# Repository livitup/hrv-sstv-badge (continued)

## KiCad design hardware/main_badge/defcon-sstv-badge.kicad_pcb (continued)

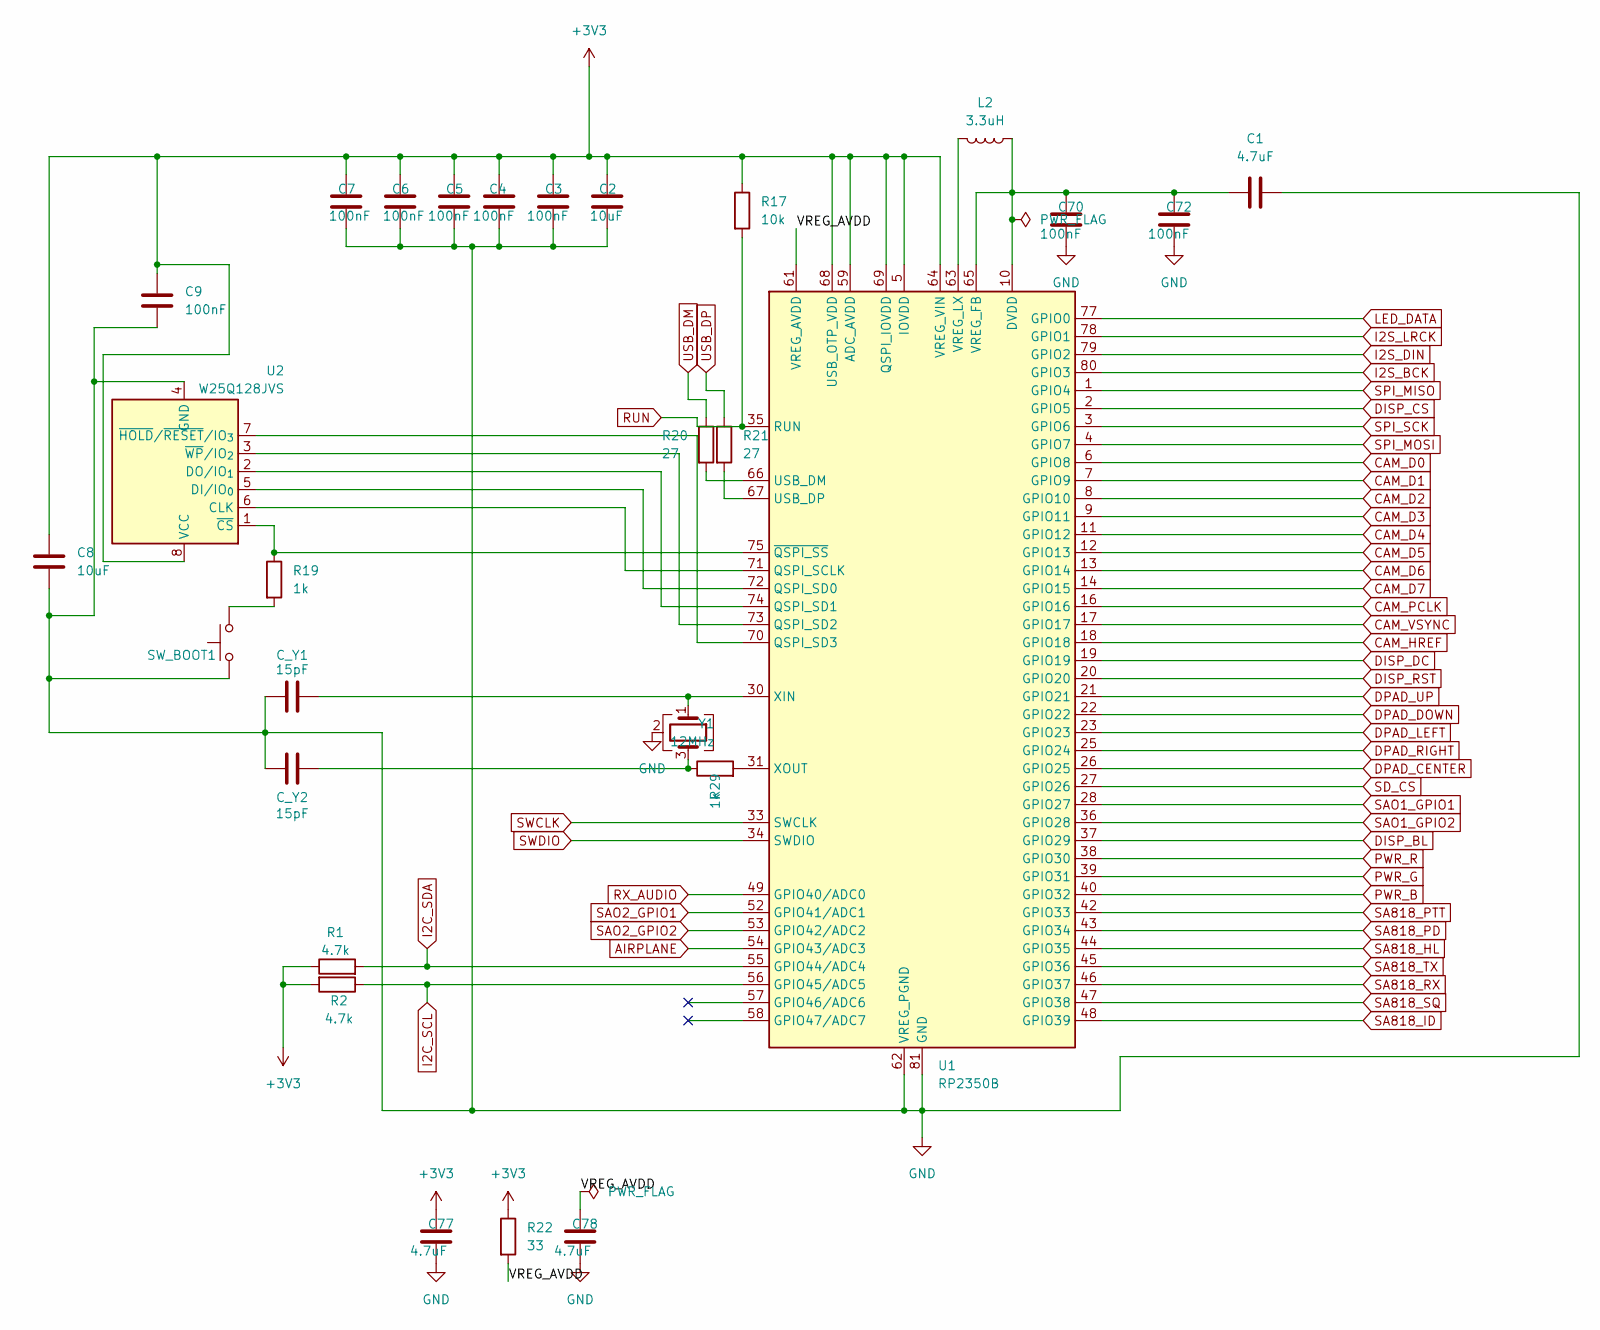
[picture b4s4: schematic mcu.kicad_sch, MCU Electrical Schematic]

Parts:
C1, C77: 4.7uF; C_0402_1005Metric_Wide
C2: 10uF; C_0603_1608Metric
C3, C4, C5, C6, C7, C9, C70, C72: 100nF; C_0402_1005Metric
C8: 10uF; C_0805_2012Metric
C78: 4.7uF; C_0402_1005Metric
C_Y1, C_Y2: 15pF; C_0402_1005Metric
L2: 3.3uH; L_Abracon_AOTA-B201610
R1, R2: 4.7k; R_0603_1608Metric
R17: 10k; R_0603_1608Metric
R19, R29: 1k; R_0402_1005Metric
R20, R21: 27; R_0402_1005Metric
R22: 33; R_0402_1005Metric
SW_BOOT1: SW_Push; SW_SPST_CK_RS282G05A3
U1: RP2350B; QFN-80-1EP_10x10mm_P0.4mm_EP3.4x3.4mm
U2: W25Q128JVS; SOIC-8_5.3x5.3mm_P1.27mm
Y1: 12MHz; Crystal_SMD_3225-4Pin_3.2x2.5mm

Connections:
+3V3: C2.1, C3.1, C4.1, C5.1, C6.1, C7.1, C8.1, C9.1, C77.1, R1.1, R2.2, R17.1, R22.1, U1.5 (IOVDD), U1.15 (IOVDD), U1.24 (IOVDD), U1.29 (IOVDD), U1.41 (IOVDD), U1.50 (IOVDD), U1.59 (ADC_AVDD), U1.60 (IOVDD), U1.64 (VREG_VIN), U1.68 (USB_OTP_VDD), U1.69 (QSPI_IOVDD), U1.76 (IOVDD), U2.8 (VCC); also elsewhere on the board
/MCU/VREG_AVDD: C78.1, R22.2, U1.61 (VREG_AVDD)
AIRPLANE: U1.54 (GPIO43/ADC3); also elsewhere on the board
CAM_D0: U1.6 (GPIO8); also elsewhere on the board
CAM_D1: U1.7 (GPIO9); also elsewhere on the board
CAM_D2: U1.8 (GPIO10); also elsewhere on the board
CAM_D3: U1.9 (GPIO11); also elsewhere on the board
CAM_D4: U1.11 (GPIO12); also elsewhere on the board
CAM_D5: U1.12 (GPIO13); also elsewhere on the board
CAM_D6: U1.13 (GPIO14); also elsewhere on the board
CAM_D7: U1.14 (GPIO15); also elsewhere on the board
CAM_HREF: U1.18 (GPIO18); also elsewhere on the board
CAM_PCLK: U1.16 (GPIO16); also elsewhere on the board
CAM_VSYNC: U1.17 (GPIO17); also elsewhere on the board
DISP_BL: U1.37 (GPIO29); also elsewhere on the board
DISP_CS: U1.2 (GPIO5); also elsewhere on the board
DISP_DC: U1.19 (GPIO19); also elsewhere on the board
DISP_RST: U1.20 (GPIO20); also elsewhere on the board
DPAD_CENTER: U1.26 (GPIO25); also elsewhere on the board
DPAD_DOWN: U1.22 (GPIO22); also elsewhere on the board
DPAD_LEFT: U1.23 (GPIO23); also elsewhere on the board
DPAD_RIGHT: U1.25 (GPIO24); also elsewhere on the board
DPAD_UP: U1.21 (GPIO21); also elsewhere on the board
I2C_SCL: R2.1, U1.56 (GPIO45/ADC5); also elsewhere on the board
I2C_SDA: R1.2, U1.55 (GPIO44/ADC4); also elsewhere on the board
I2S_BCK: U1.80 (GPIO3); also elsewhere on the board
I2S_DIN: U1.79 (GPIO2); also elsewhere on the board
I2S_LRCK: U1.78 (GPIO1); also elsewhere on the board
LED_DATA: U1.77 (GPIO0); also elsewhere on the board
unnamed: C_Y2.2, R29.1, Y1.3
unnamed: R19.2, SW_BOOT1.2
unnamed: U1.71 (QSPI_SCLK), U2.6 (CLK)
unnamed: U1.72 (QSPI_SD0), U2.5 (DI/IO_{0})
unnamed: U1.74 (QSPI_SD1), U2.2 (DO/IO_{1})
unnamed: U1.73 (QSPI_SD2), U2.3 (~WP/IO_{2})
unnamed: U1.70 (QSPI_SD3), U2.7 (~HOLD/~RESET/IO_{3})
unnamed: R20.2, U1.66 (USB_DM)
unnamed: R21.2, U1.67 (USB_DP)
unnamed: C1.1, C70.1, C72.1, L2.1, U1.10 (DVDD), U1.32 (DVDD), U1.51 (DVDD), U1.65 (VREG_FB)
unnamed: L2.2, U1.63 (VREG_LX)
unnamed: C_Y1.2, U1.30 (XIN), Y1.1
unnamed: R29.2, U1.31 (XOUT)
unnamed: R19.1, U1.75 (~QSPI_SS), U2.1 (~CS)
PWR_B: U1.40 (GPIO32); also elsewhere on the board
PWR_G: U1.39 (GPIO31); also elsewhere on the board
PWR_R: U1.38 (GPIO30); also elsewhere on the board
RUN: R17.2, U1.35 (RUN); also elsewhere on the board
RX_AUDIO: U1.49 (GPIO40/ADC0); also elsewhere on the board
SA818_HL: U1.44 (GPIO35); also elsewhere on the board
SA818_ID: U1.48 (GPIO39); also elsewhere on the board
SA818_PD: U1.43 (GPIO34); also elsewhere on the board
SA818_PTT: U1.42 (GPIO33); also elsewhere on the board
SA818_RX: U1.46 (GPIO37); also elsewhere on the board
SA818_SQ: U1.47 (GPIO38); also elsewhere on the board
SA818_TX: U1.45 (GPIO36); also elsewhere on the board
SAO1_GPIO1: U1.28 (GPIO27); also elsewhere on the board
SAO1_GPIO2: U1.36 (GPIO28); also elsewhere on the board
SAO2_GPIO1: U1.52 (GPIO41/ADC1); also elsewhere on the board
SAO2_GPIO2: U1.53 (GPIO42/ADC2); also elsewhere on the board
SD_CS: U1.27 (GPIO26); also elsewhere on the board
SPI_MISO: U1.1 (GPIO4); also elsewhere on the board
SPI_MOSI: U1.4 (GPIO7); also elsewhere on the board
SPI_SCK: U1.3 (GPIO6); also elsewhere on the board
SWCLK: U1.33 (SWCLK); also elsewhere on the board
SWDIO: U1.34 (SWDIO); also elsewhere on the board
USB_DM: R20.1; also elsewhere on the board
USB_DP: R21.1; also elsewhere on the board

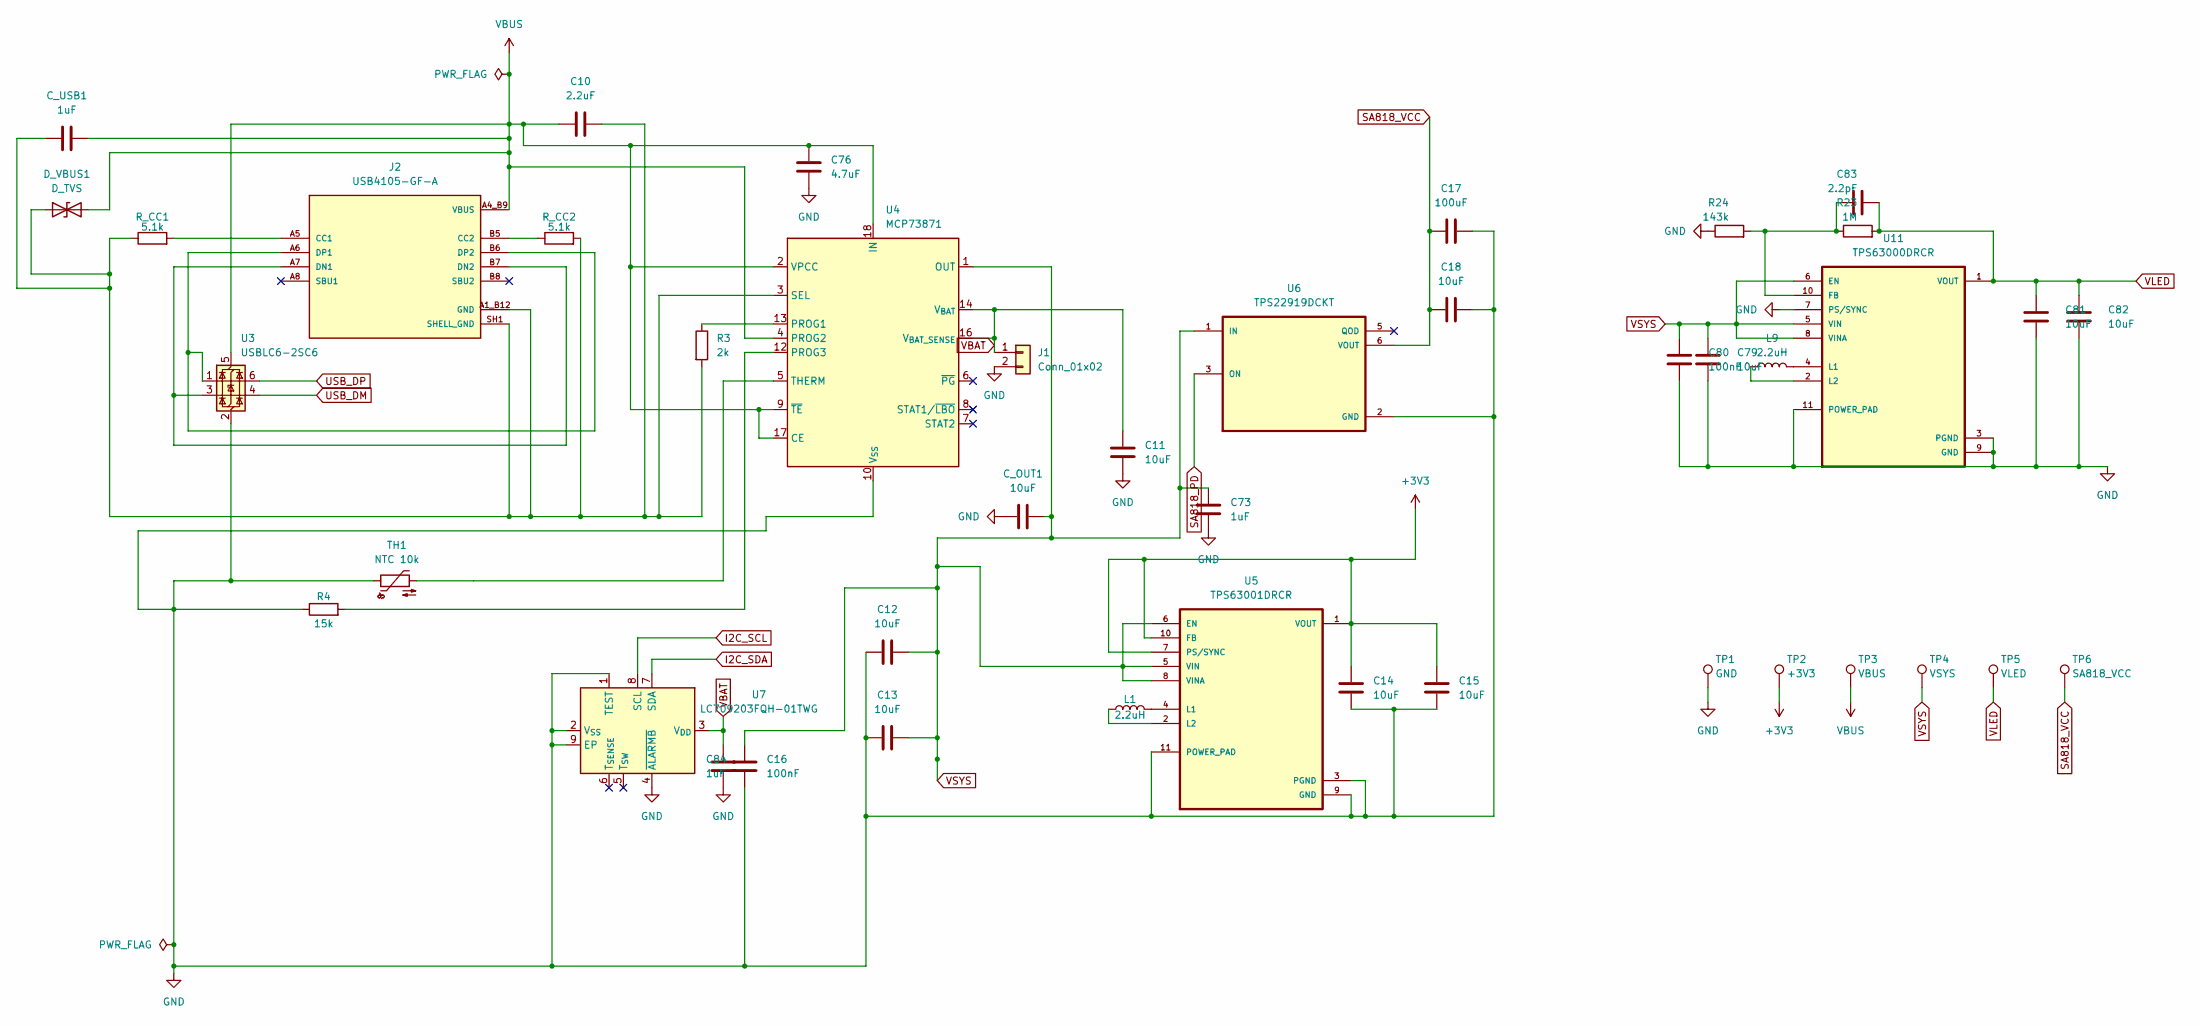
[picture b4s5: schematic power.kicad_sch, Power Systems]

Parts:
C10: 2.2uF; C_0805_2012Metric
C11, C12, C13, C14, C15, C79, C81, C82: 10uF; C_0805_2012Metric
C16, C80: 100nF; C_0402_1005Metric
C17: 100uF; C_1206_3216Metric
C18: 10uF; C_0603_1608Metric
C73: 1uF; C_0603_1608Metric
C76: 4.7uF; C_0603_1608Metric
C83: 2.2pF; C_0402_1005Metric
C84: 1uF; C_0402_1005Metric
C_OUT1: 10uF; C_0805_2012Metric
C_USB1: 1uF; C_0603_1608Metric
D_VBUS1: D_TVS; D_SOD-323
J1: Conn_01x02; JST_PH_S2B-PH-SM4-TB_1x02-1MP_P2.00mm_Horizontal
J2: USB4105-GF-A; GCT_USB4105-GF-A; PARTREV B4
L1, L9: 2.2uH; L_Taiyo-Yuden_NR-30xx_HandSoldering
R3: 2k; R_0603_1608Metric
R4: 15k; R_0603_1608Metric
R23: 1M; R_0603_1608Metric
R24: 143k; R_0603_1608Metric
R_CC1, R_CC2: 5.1k; R_0402_1005Metric
TH1: NTC 10k; R_0603_1608Metric
TP1: GND; TestPoint_Pad_D1.0mm
TP2: +3V3; TestPoint_Pad_D1.0mm
TP3: VBUS; TestPoint_Pad_D1.0mm
TP4: VSYS; TestPoint_Pad_D1.0mm
TP5: VLED; TestPoint_Pad_D1.0mm
TP6: SA818_VCC; TestPoint_Pad_D1.0mm
U3: USBLC6-2SC6; SOT-23-6
U4: MCP73871; QFN-20-1EP_4x4mm_P0.5mm_EP2.5x2.5mm
U5: TPS63001DRCR; VREG_V62_16624-01YE
U6: TPS22919DCKT; SOT65P210X110-6N
U7: LC709203FQH-01TWG; WDFN-8-1EP_4x3mm_P0.65mm_EP2.4x1.8mm
U11: TPS63000DRCR; VREG_V62_16624-01YE

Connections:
+3V3: C14.1, C15.1, TP2.1, U5.1 (VOUT), U5.7 (PS/SYNC), U5.10 (FB); also elsewhere on the board
I2C_SCL: U7.8 (SCL); also elsewhere on the board
I2C_SDA: U7.7 (SDA); also elsewhere on the board
unnamed: J2.A5 (CC1), R_CC1.2
unnamed: J2.B5 (CC2), R_CC2.1
unnamed: J2.A7 (DN1), J2.B7 (DN2), U3.3 (I/O2)
unnamed: J2.A6 (DP1), J2.B6 (DP2), U3.1 (I/O1)
unnamed: R3.1, U4.13 (PROG1)
unnamed: R4.2, U4.12 (PROG3)
unnamed: TH1.2, U4.5 (THERM)
unnamed: L1.2, U5.4 (L1)
unnamed: L1.1, U5.2 (L2)
unnamed: C83.1, R23.1, R24.2, U11.10 (FB)
unnamed: L9.2, U11.4 (L1)
unnamed: L9.1, U11.2 (L2)
SA818_PD: U6.3 (ON); also elsewhere on the board
SA818_VCC: C17.1, C18.1, TP6.1, U6.6 (VOUT); also elsewhere on the board
USB_DM: U3.4 (I/O2); also elsewhere on the board
USB_DP: U3.6 (I/O1); also elsewhere on the board
VBAT: C11.1, C84.1, J1.1, U4.14 (V_{BAT}), U4.15 (V_{BAT}), U4.16 (V_{BAT_SENSE}), U7.3 (V_{DD})
VBUS: C10.1, C76.1, C_USB1.2, D_VBUS1.2 (A2), J2.A4_B9 (VBUS), J2.B4_A9 (VBUS), TP3.1, U3.5 (VBUS), U4.2 (VPCC), U4.4 (PROG2), U4.9 (~TE), U4.17 (CE), U4.18 (IN), U4.19 (IN)
VLED: C81.1, C82.1, C83.2, R23.2, TP5.1, U11.1 (VOUT); also elsewhere on the board
VSYS: C12.1, C13.2, C16.1, C73.1, C79.1, C80.1, C_OUT1.1, TP4.1, U4.1 (OUT), U4.20 (OUT), U5.5 (VIN), U5.6 (EN), U5.8 (VINA), U6.1 (IN), U11.5 (VIN), U11.6 (EN), U11.8 (VINA)

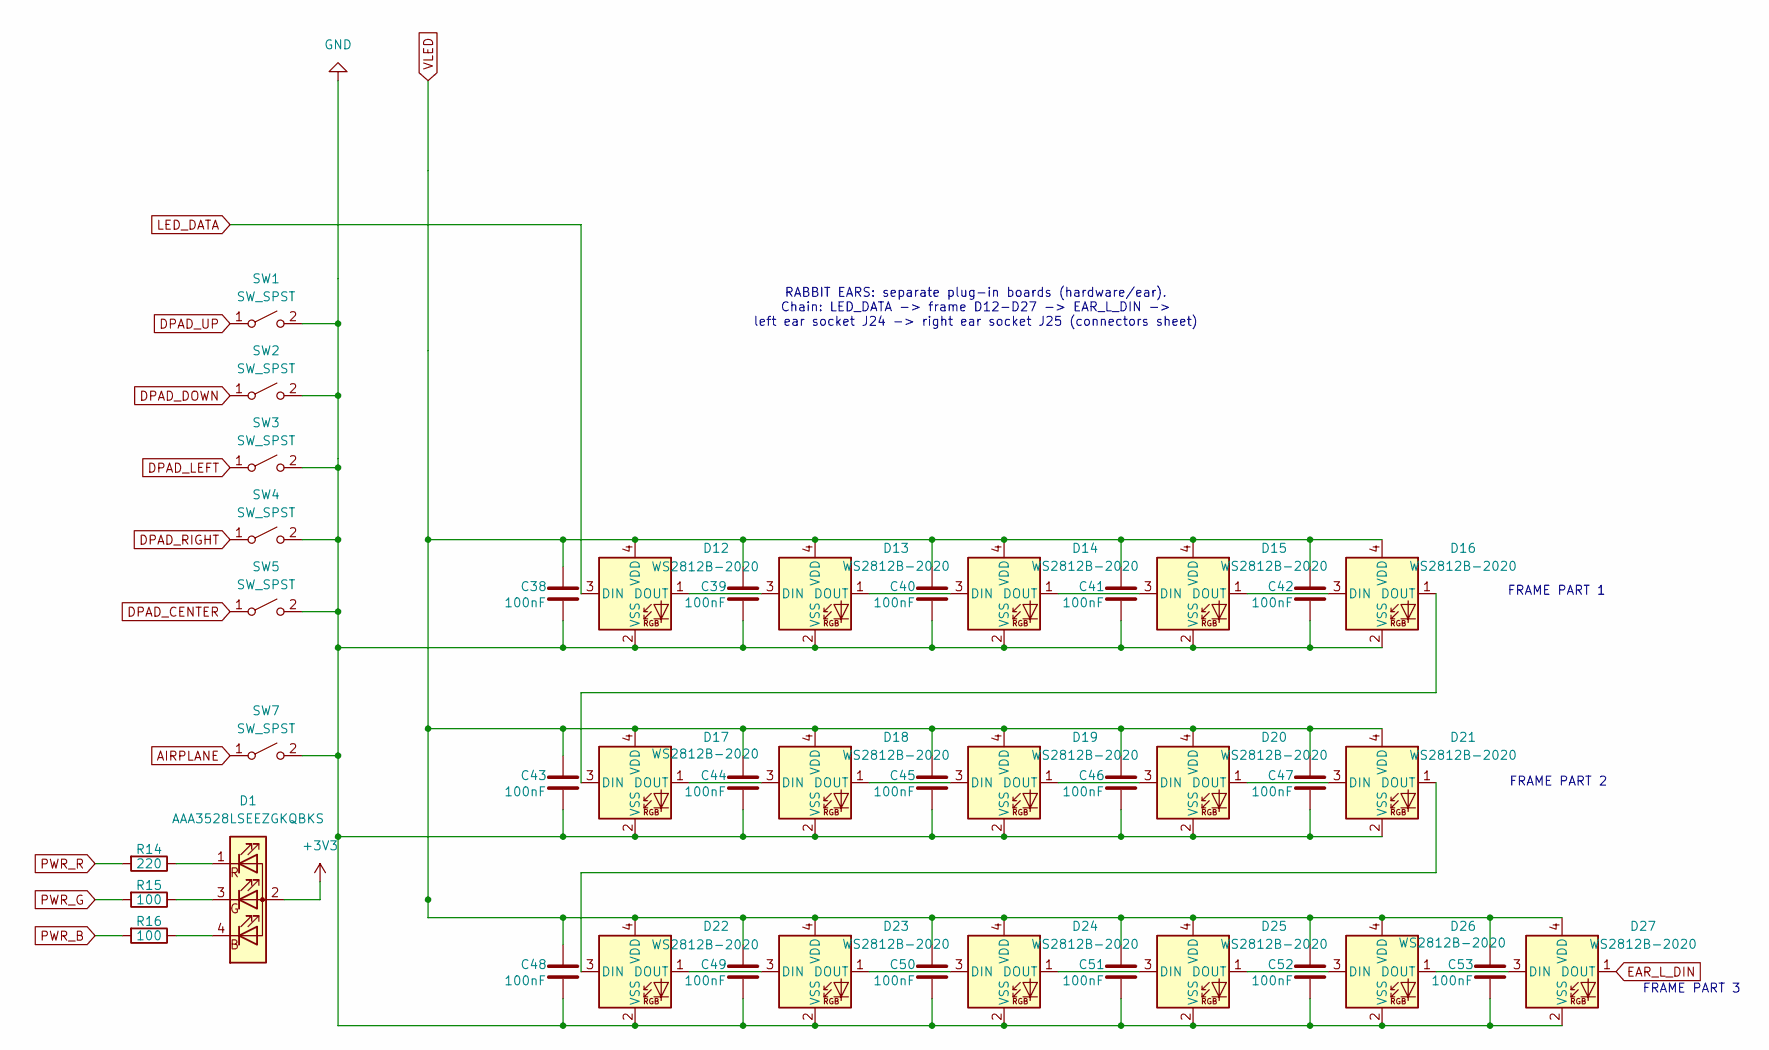
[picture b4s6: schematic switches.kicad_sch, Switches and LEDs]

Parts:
C38, C39, C40, C41, C42, C43, C44, C45, C46, C47, C48, C49, C50, C51, C52, C53: 100nF; C_0402_1005Metric
D1: AAA3528LSEEZGKQBKS; LED_Kingbright_AAA3528ESGCT
D12, D13, D14, D15, D16, D17, D18, D19, D20, D21, D22, D23, D24, D25, D26, D27: WS2812B-2020; LED_WS2812B-2020_PLCC4_2.0x2.0mm
R14: 220; R_0603_1608Metric
R15, R16: 100; R_0603_1608Metric
SW1, SW2, SW3, SW4, SW5: SW_SPST; SW_PUSH_6mm_H5mm
SW7: SW_SPST; SW_Slide_SPDT_Angled_CK_OS102011MA1Q

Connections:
+3V3: D1.2 (A); also elsewhere on the board
AIRPLANE: SW7.1 (A); also elsewhere on the board
DPAD_CENTER: SW5.1 (A); also elsewhere on the board
DPAD_DOWN: SW2.1 (A); also elsewhere on the board
DPAD_LEFT: SW3.1 (A); also elsewhere on the board
DPAD_RIGHT: SW4.1 (A); also elsewhere on the board
DPAD_UP: SW1.1 (A); also elsewhere on the board
EAR_L_DIN: D27.1 (VDD); also elsewhere on the board
LED_DATA: D12.3 (VSS); also elsewhere on the board
unnamed: D1.4 (B), R16.1
unnamed: D1.3 (G), R15.1
unnamed: D1.1 (R), R14.1
unnamed: D12.1 (VDD), D13.3 (VSS)
unnamed: D13.1 (VDD), D14.3 (VSS)
unnamed: D14.1 (VDD), D15.3 (VSS)
unnamed: D15.1 (VDD), D16.3 (VSS)
unnamed: D16.1 (VDD), D17.3 (VSS)
unnamed: D17.1 (VDD), D18.3 (VSS)
unnamed: D18.1 (VDD), D19.3 (VSS)
unnamed: D19.1 (VDD), D20.3 (VSS)
unnamed: D20.1 (VDD), D21.3 (VSS)
unnamed: D21.1 (VDD), D22.3 (VSS)
unnamed: D22.1 (VDD), D23.3 (VSS)
unnamed: D23.1 (VDD), D24.3 (VSS)
unnamed: D24.1 (VDD), D25.3 (VSS)
unnamed: D25.1 (VDD), D26.3 (VSS)
unnamed: D26.1 (VDD), D27.3 (VSS)
PWR_B: R16.2; also elsewhere on the board
PWR_G: R15.2; also elsewhere on the board
PWR_R: R14.2; also elsewhere on the board
VLED: C38.1, C39.1, C40.1, C41.1, C42.1, C43.1, C44.1, C45.1, C46.1, C47.1, C48.1, C49.1, C50.1, C51.1, C52.1, C53.1, D12.4 (DIN), D13.4 (DIN), D14.4 (DIN), D15.4 (DIN), D16.4 (DIN), D17.4 (DIN), D18.4 (DIN), D19.4 (DIN), D20.4 (DIN), D21.4 (DIN), D22.4 (DIN), D23.4 (DIN), D24.4 (DIN), D25.4 (DIN), D26.4 (DIN), D27.4 (DIN); also elsewhere on the board

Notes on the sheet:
FRAME PART 2
FRAME PART 3
FRAME PART 1
RABBIT EARS: separate plug-in boards (hardware/ear). Chain: LED_DATA -> frame D12-D27 -> EAR_L_DIN -> left ear socket J24 -> right ear socket J25 (connectors sheet)

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
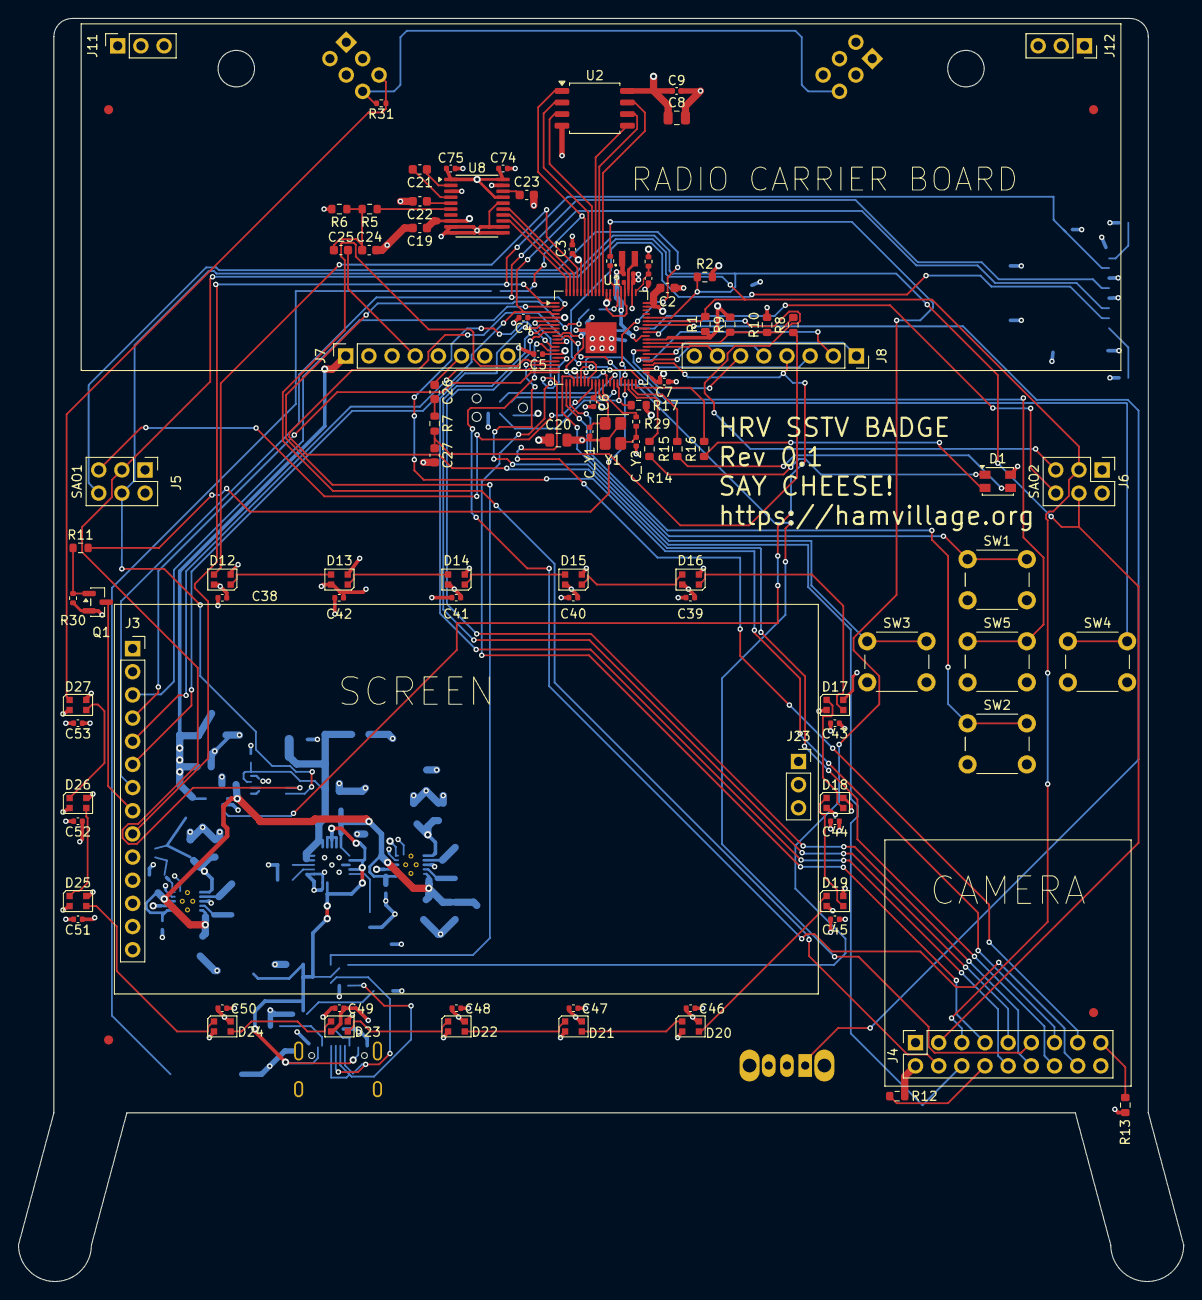
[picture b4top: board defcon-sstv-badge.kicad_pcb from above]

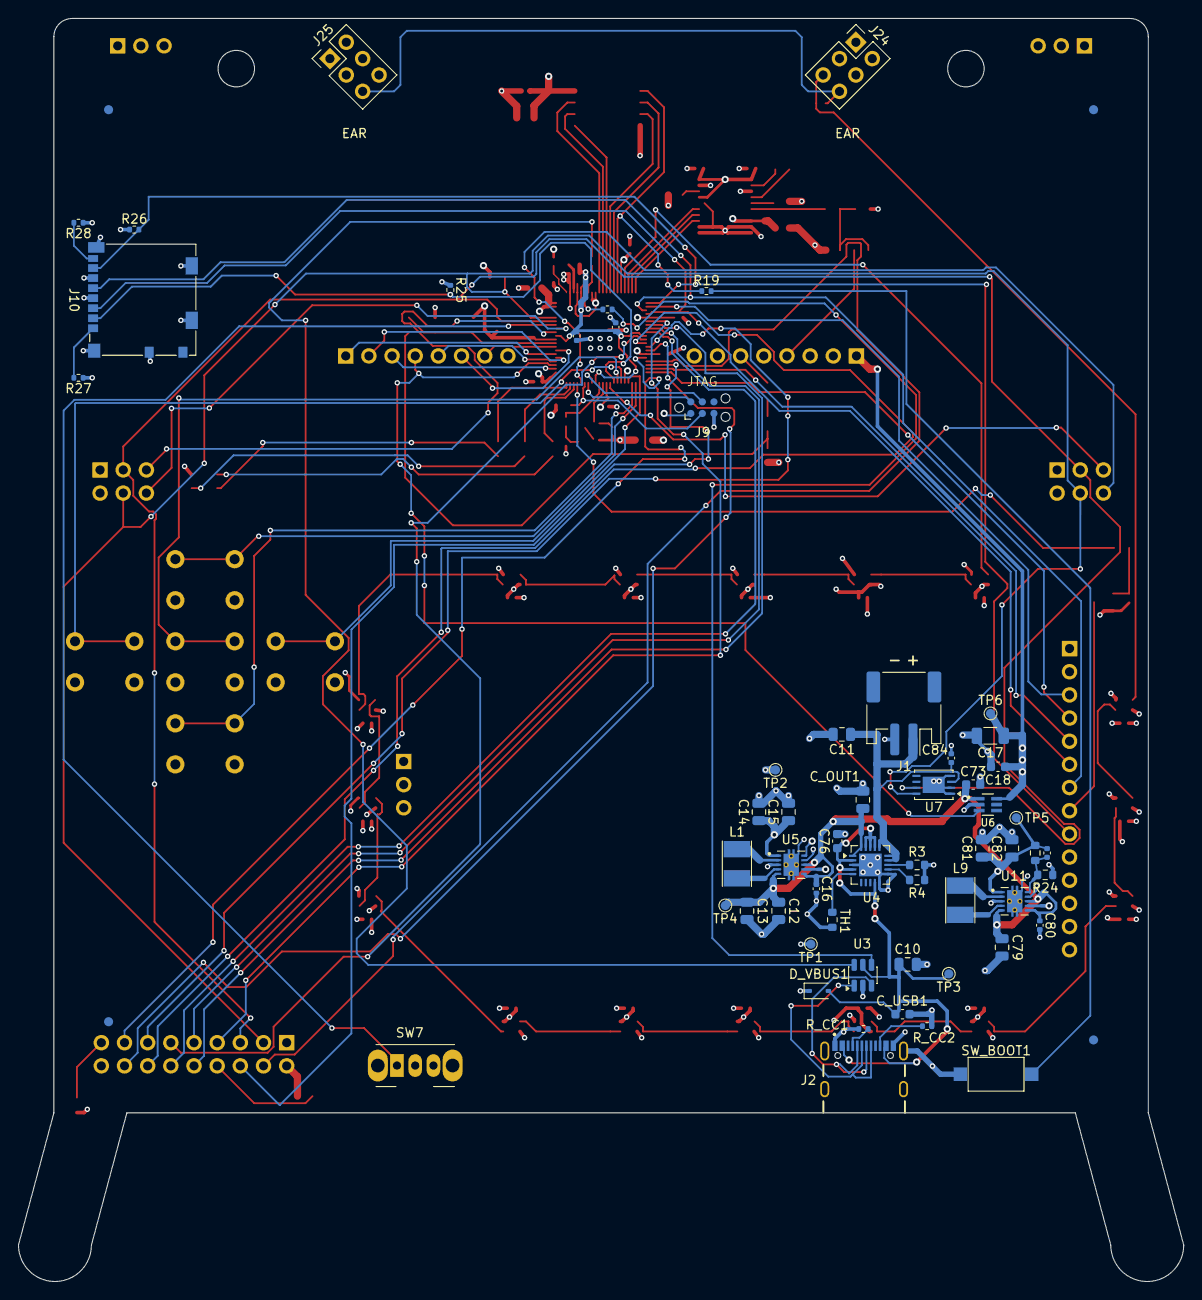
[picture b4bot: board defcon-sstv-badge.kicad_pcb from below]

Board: 4 copper layers, 127.8 x 138.5 mm, 164 parts (61 on the bottom side), 121 nets.

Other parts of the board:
FID1, FID2, FID3, FID4, FID5, FID6, FID7, FID8: Fiducial; Fiducial_1mm_Mask2mm
H1, H2: Lanyard hole 4mm; MountingHole_4mm

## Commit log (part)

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2025-09-02 Initial commit, full documentation suite
2025-09-02 Add claude context
2025-09-04 Update documentation
2025-09-04 Update build defaults
2025-09-04 add details on non-ham lockdown and V/UHF swap
2025-09-04 add details to context about SSTV timing requirements and core usage and updated make defaults
2026-02-07 Update all the documentation.
2026-02-08 ignore autosave
2026-02-08 ignore autosave maybe for real
2026-02-08 mcu power layout
2026-02-08 add oscilator
2026-02-08 add flash reader
2026-02-08 ignore kicad backup files
2026-02-08 add bootloader switch
2026-02-08 add I2C pullups
2026-02-09 add charging controller
2026-02-09 add buck/boost
2026-02-09 add TPS22919 for powering off the radio
2026-02-09 add battery fuel gauge
2026-02-09 RX Filter
2026-02-09 TX Filter pt. 2
2026-02-10 camera/display sheet
2026-02-10 Buttons and LEDs
2026-02-11 MCP GPIO pins to labels
2026-02-16 all design sheets complete, ERC clean
2026-02-16 add BOM
2026-02-16 update BOM and documentation
2026-02-16 add carrier boards for SA818 modules
2026-02-16 add raw BOM
2026-02-16 split documentation between notebook and final state docs
2026-02-16 add footprints and break carrier boards out into standalone projects
2026-02-17 vhf board layout
2026-03-16 VHF Carrier Board
2026-03-16 UHF carrier board
2026-03-16 move main badge files to subdirectory
2026-03-22 main board done except for placing LEDs and drawing ears... I think
2026-03-22 screen LEDs placed, photo button removed
2026-03-23 main badge final updates
2026-03-23 documentation update
2026-03-23 update text on carrier boards
2026-03-23 update the PCB for tv cabinet feet
2026-03-23 documentation updates
2026-03-23 add routing docs
2026-03-23 inital power cap placement
2026-03-23 most of the load capacitors
2026-03-25 USB port and chip routed
2026-03-25 U5 routing complete
2026-03-29 work in progress power subsystems routing
2026-03-31 traces all fubar, might delete them all and start over.
2026-04-01 clean PCB, prior to rewiring for clean board design
2026-04-01 updated MCU pin layout
2026-04-27 wip routing
2026-04-27 more routing, 29 to go...
2026-05-01 routing. 2 nodes to go...
2026-05-01 all traces complete, but lots of DRC warnings to fix
2026-05-01 connect J7 pin 8 to GND
2026-05-01 routing and component bug fixes
2026-05-10 main board finished, no DRC errors
